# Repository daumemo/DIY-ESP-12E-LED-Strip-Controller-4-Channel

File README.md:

# DIY-ESP-12E-LED-Strip-Controller-4-Channel

These are the files for a DIY LED strip controller's project.

More information you can find at: https://daumemo.com/diy-esp8266-led-strip-controller-4-channel-12v/

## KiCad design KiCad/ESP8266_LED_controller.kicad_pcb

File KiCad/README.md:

# DIY-ESP-12E-LED-Strip-Controller-4-Channel

Here are the KiCad project files. Project was created with 4.0.6 version.
PART_LIST.csv contains all parts needed for the project

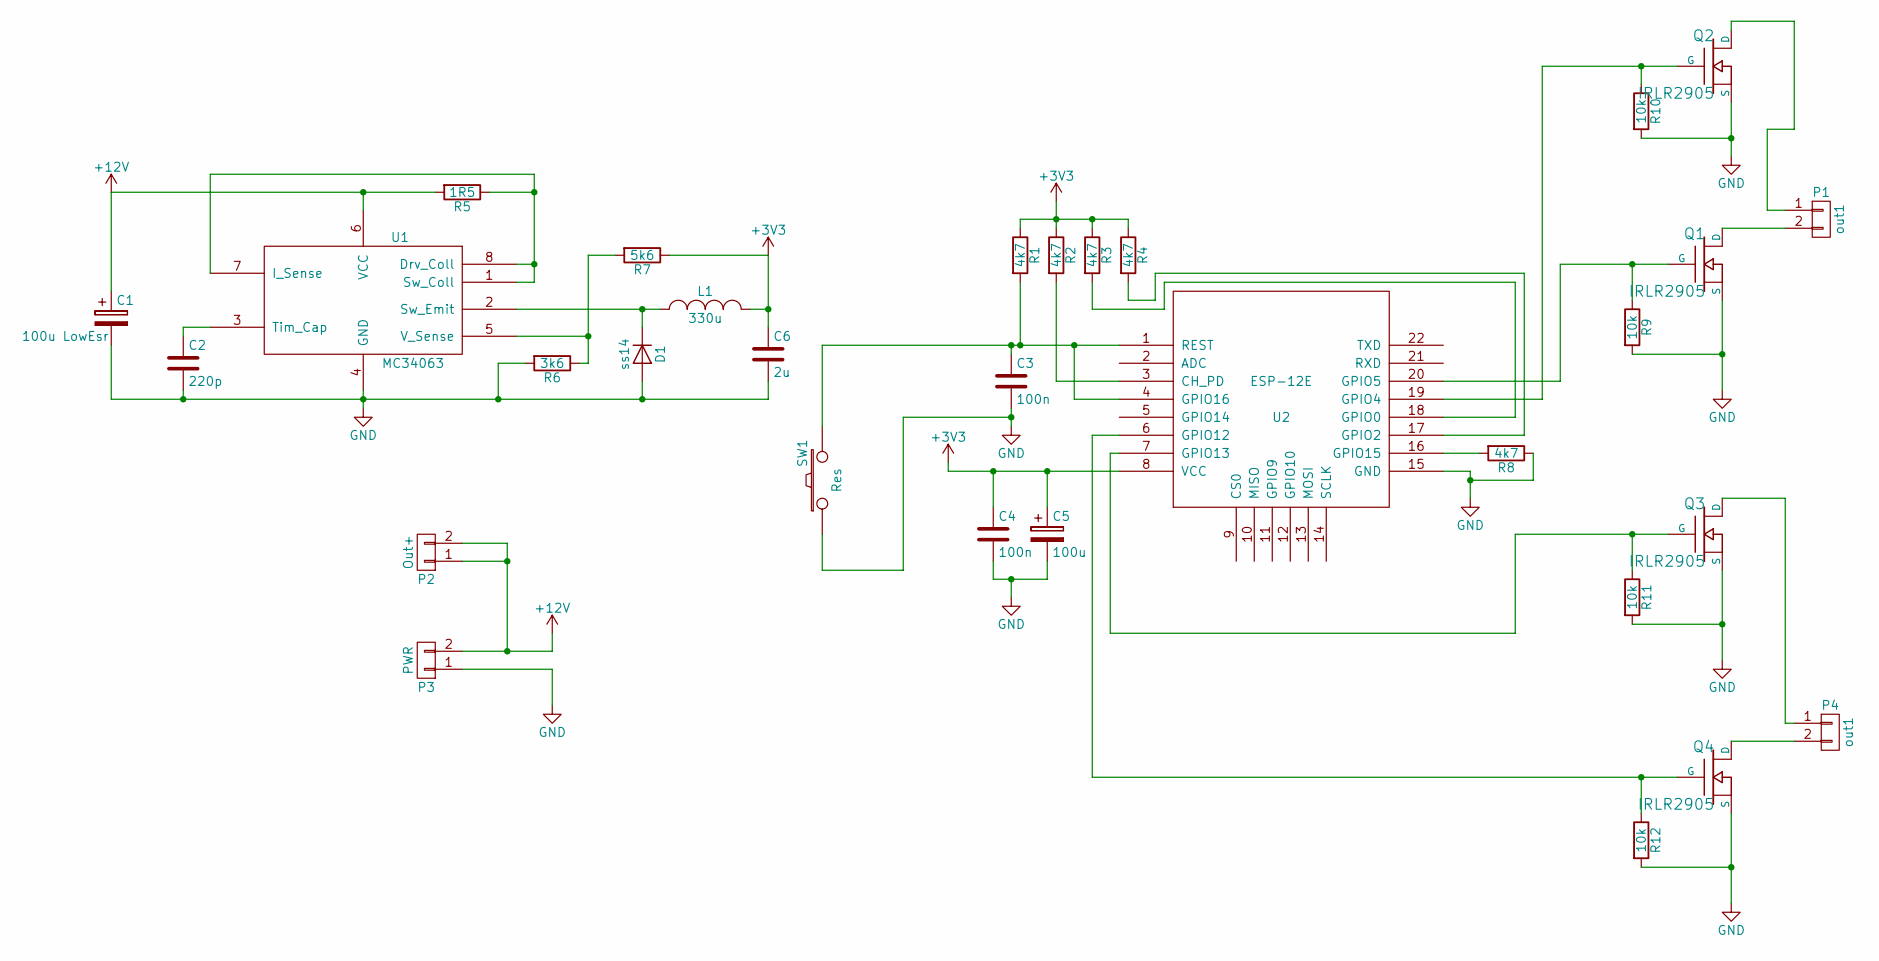
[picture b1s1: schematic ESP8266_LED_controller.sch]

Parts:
C1: 100u LowEsr; CP_Radial_D6.3mm_P2.50mm
C2: 220p; C_0603
C3, C4: 100n; C_0603
C5: 100u; CP_Tantalum_Case-B_EIA-3528-21_Hand
C6: 2u; C_0603
D1: ss14; D_SMA
L1: 330u; Inductor_Wurth_HCI-5040
P1, P4: out1; TerminalBlock_bornier-2_P5.08mm
P2: Out+; TerminalBlock_bornier-2_P5.08mm
P3: PWR; TerminalBlock_bornier-2_P5.08mm
Q1, Q2, Q3, Q4: IRLR2905; TO-252-2
R1, R2, R3, R4, R8: 4k7; R_0603
R5: 1R5; R_0603
R6: 3k6; R_0603
R7: 5k6; R_0603
R9, R10, R11, R12: 10k; R_0603
SW1: Res; SW_Tactile_SPST_Angled_PTS645Vx39-2LFS
U1: MC34063; SO-8_5.3x6.2mm_Pitch1.27mm
U2: ESP-12E; Esp-12E

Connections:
+3V3: C4.1, C5.1, C6.1, L1.2, R1.1, R2.1, R3.1, R4.1, R7.1, U2.8 (VCC)
+12V: C1.1, P2.1, P2.2, P3.2, R5.2, U1.6 (VCC)
GND: C1.2, C2.2, C3.2, C4.2, C5.2, C6.2, D1.2 (A), P3.1, Q1.S, Q2.S, Q3.S, Q4.S, R6.2, R8.1, R9.2, R10.2, R11.2, R12.2, SW1.1, U1.4 (GND), U2.15 (GND)
unnamed: C2.1, U1.3 (Tim_Cap)
unnamed: C3.1, R1.2, SW1.2, U2.1 (REST), U2.4 (GPIO16)
unnamed: D1.1 (K), L1.1, U1.2 (Sw_Emit)
unnamed: P1.1, Q2.D
unnamed: P1.2, Q1.D
unnamed: P4.1, Q3.D
unnamed: P4.2, Q4.D
unnamed: Q1.G, R9.1, U2.20 (GPIO5)
unnamed: Q2.G, R10.1, U2.19 (GPIO4)
unnamed: Q3.G, R11.1, U2.7 (GPIO13)
unnamed: Q4.G, R12.1, U2.6 (GPIO12)
unnamed: R2.2, U2.3 (CH_PD)
unnamed: R3.2, U2.18 (GPIO0)
unnamed: R4.2, U2.17 (GPIO2)
unnamed: R5.1, U1.1 (Sw_Coll), U1.7 (I_Sense), U1.8 (Drv_Coll)
unnamed: R6.1, R7.2, U1.5 (V_Sense)
unnamed: R8.2, U2.16 (GPIO15)

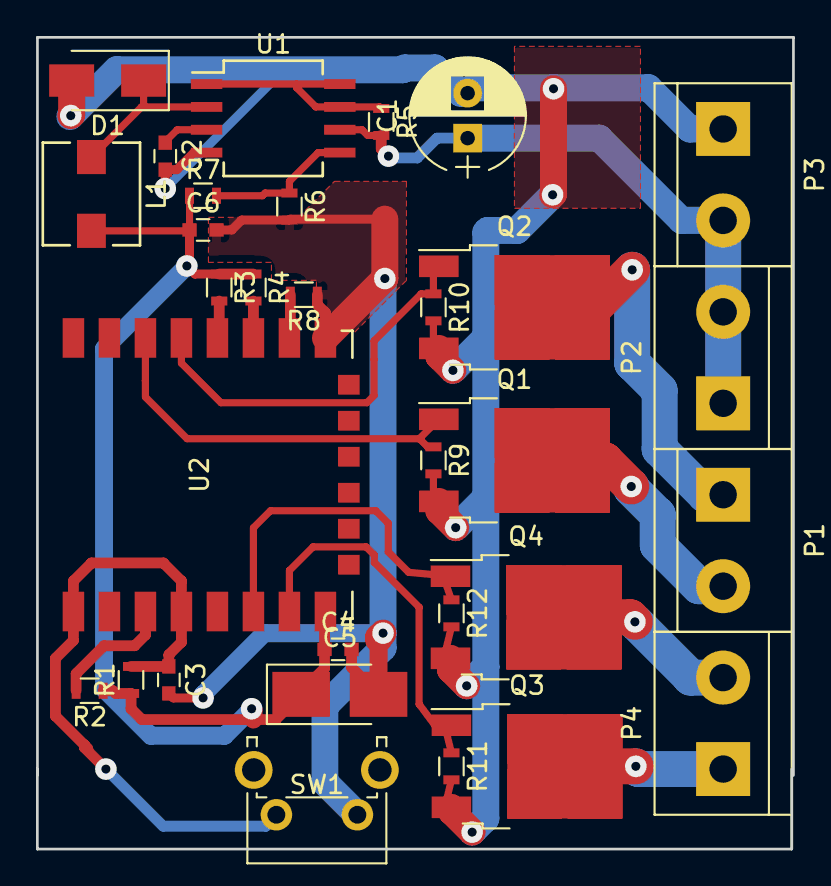
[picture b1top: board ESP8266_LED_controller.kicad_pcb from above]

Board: 2 copper layers, 42.0 x 45.1 mm, 31 parts (0 on the bottom side), 20 nets.

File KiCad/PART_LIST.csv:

Id;Designator;Package;Quantity;Designation;
1;C2;C_0603;1;220p;
2;C3,C4;C_0603;2;100n;
3;C6;C_0603;1;2u;
4;D1;D_SMA;1;ss14;
5;L1;Inductor_Wurth_HCI-5040;1;330u;
6;Q1,Q2,Q3,Q4;TO-252-2;4;IRLR2905;
7;R1,R2,R3,R4,R8;R_0603;5;4k7;
8;R5;R_0603;1;1R5;
9;R6;R_0603;1;3k6;
10;R7;R_0603;1;5k6;
11;R9,R10,R11,R12;R_0603;4;10k;
12;SW1;SW_Tactile_SPST_Angled_PTS645Vx39-2LFS;1;Res;
13;U1;SO-8_5.3x6.2mm_Pitch1.27mm;1;MC34063;
14;U2;Esp-12E;1;ESP-12E;
15;C1;CP_Radial_D6.3mm_P2.50mm;1;100u;Low ESR 16 V minimum
16;C5;CP_Tantalum_Case-B_EIA-3528-21_Hand;1;100u;
17;P1,P4;TerminalBlock_bornier-2_P5.08mm;2;out1;
18;P2;TerminalBlock_bornier-2_P5.08mm;1;Out+;
19;P3;TerminalBlock_bornier-2_P5.08mm;1;PWR;

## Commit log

2019-07-30 Initial
2019-07-30 changed url
2019-07-30 added img
2019-07-30 added part list
2019-07-30 added text
